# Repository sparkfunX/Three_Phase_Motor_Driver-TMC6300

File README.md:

SparkFun 3-Phase BLDC Motor Driver - TMC6300
========================================

[*SparkFun 3-Phase BLDC Motor Driver - TMC6300(ROB-21220)*](https://www.sparkfun.com/products/21220)

The TMC6300 from Trinamic is a powerful, yet easy to use three phase brushless DC (BLDC) motor driver. Separate high side and low side controls allow for incredible control up to 2A of current. The driver is temperature and short circuit protected with a diagnostic output pin to indicate system issues. With an operating voltage down to 2V, the TMC6300 is suitable for battery powered designs.

We've designed an innovative 2 sided, 4 layer breakout board to make hookup as easy as possible. The board is mounted with LEDs and labels facing up, IC down. This allows the thermal pad on the board to be access if cooling is required. 

Controlling 3-phase BLDC motors is not trivial. This board requires 6 PWM signals to fully control one motor. We've found the [*Arduino Simple Field Oriented Control*](https://docs.simplefoc.com/) library to be very good. The [open loop example](https://github.com/simplefoc/Arduino-FOC/blob/master/examples/motion_control/open_loop_motor_control/open_loop_velocity_example/open_loop_velocity_example.ino) combined with the [6 channel PWM method](https://docs.simplefoc.com/bldcdriver6pwm) and *every* PWM pin on the Arduino Uno gets this board working. Note the [pairs of PWM pins](https://docs.simplefoc.com/bldcdriver6pwm) that must be used. 

This board was designed to control our [3-phase Brushless Gimbal Stabilizer Motor](https://www.sparkfun.com/products/20441) but can be used with any 3-phase motor up to 2A.

SparkFun labored with love to create this code. Feel like supporting open source hardware? 
Buy a [breakout board](https://www.sparkfun.com/products/21220) from SparkFun!

Repository Contents
-------------------

* **/Documents** - Datasheet and User Manual
* **/Hardware** - Eagle design files (.brd, .sch)

License Information
-------------------

This product is _**open source**_! 

Please review the LICENSE.md file for license information. 

If you have any questions or concerns on licensing, please contact techsupport@sparkfun.com.

Please use, reuse, and modify these files as you see fit. Please maintain attribution to SparkFun Electronics and release any derivative under the same license.

Distributed as-is; no warranty is given.

- Your friends at SparkFun.

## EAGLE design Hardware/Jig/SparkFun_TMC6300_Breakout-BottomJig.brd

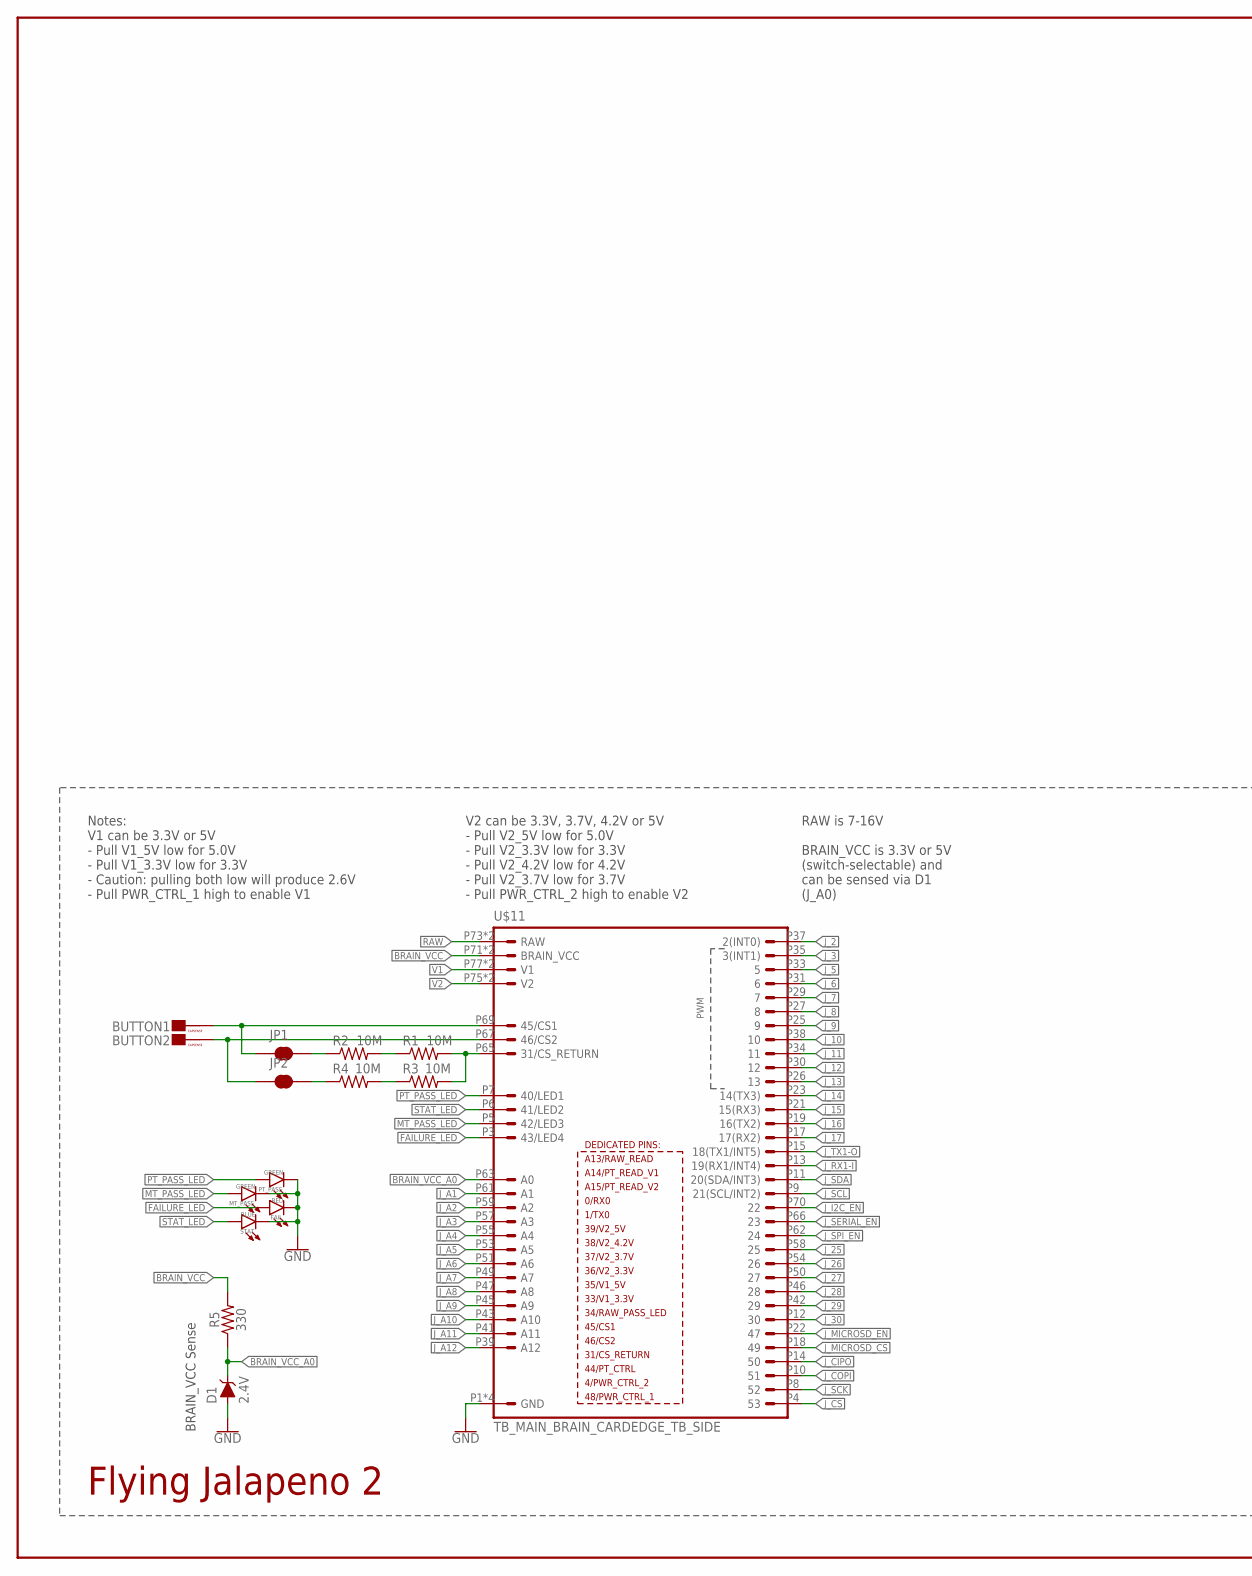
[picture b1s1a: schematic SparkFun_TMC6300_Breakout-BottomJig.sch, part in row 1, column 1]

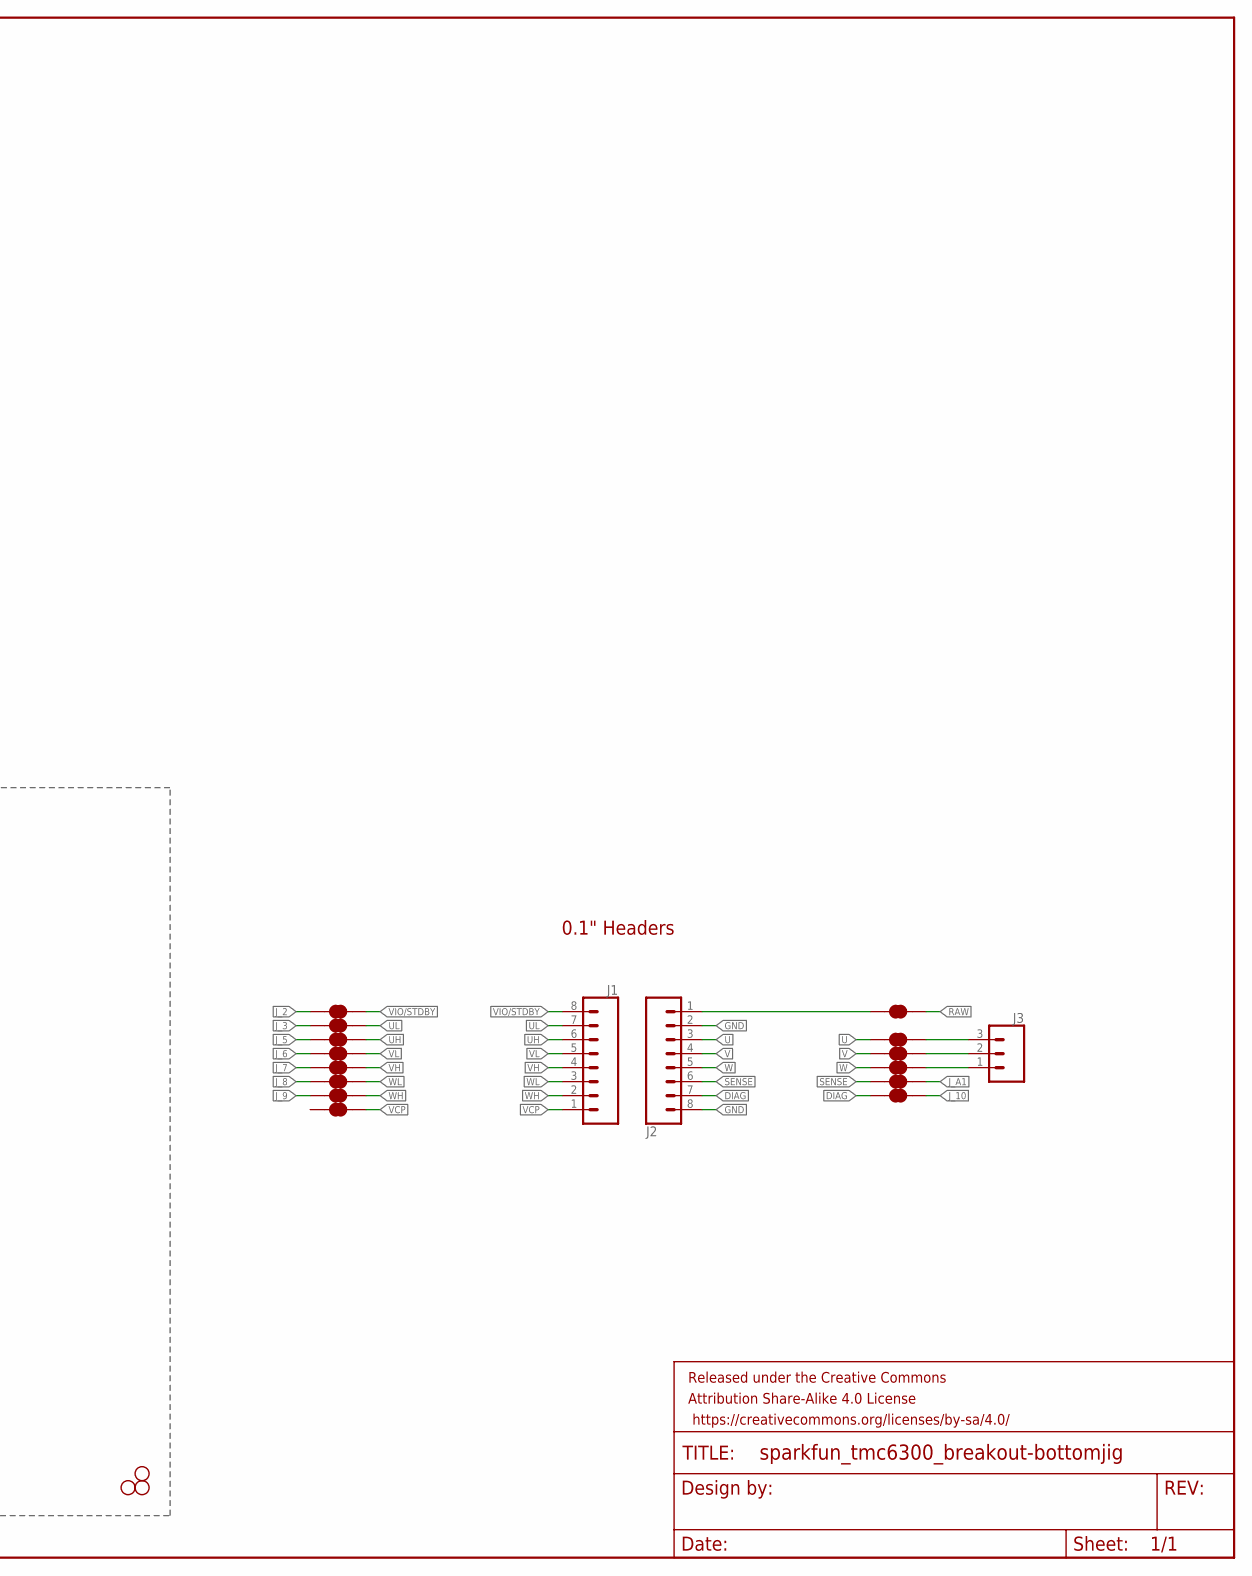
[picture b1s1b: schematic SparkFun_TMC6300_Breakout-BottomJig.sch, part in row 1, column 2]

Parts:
BUTTON1, BUTTON2: CAPSENSE_BUTTON_PAD_ONLYV2_SMALL; CAPSENSE_BUTTON_PAD_ONLY_SM
D1: 2.4V; SOD-323
FAIL: RED; LED-1206
FRAME2: FRAME-LEDGER; CREATIVE_COMMONS
H1, H3, H4: STAND-OFF
J1, J2: CONN_08LOCK_NO_SILK; 1X08_LOCK_NO_SILK
J3: CONN_031X03_NO_SILK; 1X03_NO_SILK
JP1, JP2: JUMPER-SMT_2_NC_TRACE_SILK; SMT-JUMPER_2_NC_TRACE_SILK
J_SCL6, J_SCL7, J_SCL8: JUMPER-SMT_2_NC_TRACE_NO-SILK; SMT-JUMPER_2_NC_TRACE_NO-SILK
J_SDA1, J_SDA2, J_SDA3, J_SDA4, J_SDA5, J_SDA6, J_SDA7, J_SDA8, J_SDA9, J_SDA10, J_SDA11: JUMPER-SMT_2_NC_TRACE_NO-SILK; SMT-JUMPER_2_NC_TRACE_NO-SILK
MT_PASS: GREEN; LED-1206
PT_PASS: GREEN; LED-1206
R1, R2, R3, R4: 10M; 0603
R5: 330; 0603
STAT: BLUE; LED-1206
U$11: TB_MAIN_BRAIN_CARDEDGE_TB_SIDE; TB_CARDEDGE

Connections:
BRAIN_VCC: R5.2, U$11.P71 (BRAIN_VCC), U$11.P72 (BRAIN_VCC)
BRAIN_VCC_A0: D1.C, R5.1, U$11.P63 (A0)
DIAG: J2.7, J_SDA7.1
FAILURE_LED: FAIL.A, U$11.P3 (43/LED4)
GND: D1.A, FAIL.C, J2.2, J2.8, MT_PASS.C, PT_PASS.C, STAT.C, U$11.P1 (GND), U$11.P2 (GND), U$11.P79 (GND), U$11.P80 (GND)
J_2: J_SCL8.1, U$11.P37 (2(INT0))
J_3: J_SCL6.1, U$11.P35 (3(INT1))
J_5: J_SCL7.1, U$11.P33 (5)
J_6: J_SDA2.1, U$11.P31 (6)
J_7: J_SDA3.1, U$11.P29 (7)
J_8: J_SDA4.1, U$11.P27 (8)
J_9: J_SDA5.1, U$11.P25 (9)
J_10: J_SDA7.2, U$11.P38 (10)
J_11: U$11.P34 (11)
J_12: U$11.P30 (12)
J_13: U$11.P26 (13)
J_14: U$11.P23 (14(TX3))
J_15: U$11.P21 (15(RX3))
J_16: U$11.P19 (16(TX2))
J_17: U$11.P17 (17(RX2))
J_25: U$11.P58 (25)
J_26: U$11.P54 (26)
J_27: U$11.P50 (27)
J_28: U$11.P46 (28)
J_29: U$11.P42 (29)
J_30: U$11.P12 (30)
J_A1: J_SDA8.2, U$11.P61 (A1)
J_A2: U$11.P59 (A2)
J_A3: U$11.P57 (A3)
J_A4: U$11.P55 (A4)
J_A5: U$11.P53 (A5)
J_A6: U$11.P51 (A6)
J_A7: U$11.P49 (A7)
J_A8: U$11.P47 (A8)
J_A9: U$11.P45 (A9)
J_A10: U$11.P43 (A10)
J_A11: U$11.P41 (A11)
J_A12: U$11.P39 (A12)
J_CIPO: U$11.P14 (50)
J_COPI: U$11.P10 (51)
J_CS: U$11.P4 (53)
J_I2C_EN: U$11.P70 (22)
J_MICROSD_!CS!: U$11.P18 (49)
J_MICROSD_EN: U$11.P22 (47)
J_RX1-I: U$11.P13 (19(RX1/INT4))
J_SCK: U$11.P8 (52)
J_SCL: U$11.P9 (21(SCL/INT2))
J_SDA: U$11.P11 (20(SDA/INT3))
J_SERIAL_EN: U$11.P66 (23)
J_SPI_EN: U$11.P62 (24)
J_TX1-O: U$11.P15 (18(TX1/INT5))
MT_PASS_LED: MT_PASS.A, U$11.P5 (42/LED3)
unnamed: J3.1, J_SDA9.2
unnamed: R1.2, R3.2, U$11.P65 (31/CS_RETURN)
unnamed: R1.1, R2.2
unnamed: J3.2, J_SDA10.2
unnamed: J3.3, J_SDA11.2
unnamed: J2.1, J_SDA1.1
unnamed: BUTTON1.CAPSENSE_PAD, JP1.1, U$11.P69 (45/CS1)
unnamed: R3.1, R4.2
unnamed: JP2.2, R4.1
unnamed: BUTTON2.CAPSENSE_PAD, JP2.1, U$11.P67 (46/CS2)
unnamed: JP1.2, R2.1
PT_PASS_LED: PT_PASS.A, U$11.P7 (40/LED1)
RAW: J_SDA1.2, U$11.P73 (RAW), U$11.P74 (RAW)
SENSE: J2.6, J_SDA8.1
STAT_LED: STAT.A, U$11.P6 (41/LED2)
U: J2.3, J_SDA11.1
UH: J1.6, J_SCL7.2
UL: J1.7, J_SCL6.2
V: J2.4, J_SDA10.1
V1: U$11.P77 (V1), U$11.P78 (V1)
V2: U$11.P75 (V2), U$11.P76 (V2)
VCP: J1.1, J_SDA6.2
VH: J1.4, J_SDA3.2
VIO/!STDBY!: J1.8, J_SCL8.2
VL: J1.5, J_SDA2.2
W: J2.5, J_SDA9.1
WH: J1.2, J_SDA5.2
WL: J1.3, J_SDA4.2

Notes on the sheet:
0.1" Headers
Flying Jalapeno 2
Notes: V1 can be 3.3V or 5V - Pull V1_5V low for 5.0V - Pull V1_3.3V low for 3.3V - Caution: pulling both low will produce 2.6V - Pull PWR_CTRL_1 high to enable V1
V2 can be 3.3V, 3.7V, 4.2V or 5V - Pull V2_5V low for 5.0V - Pull V2_3.3V low for 3.3V - Pull V2_4.2V low for 4.2V - Pull V2_3.7V low for 3.7V - Pull PWR_CTRL_2 high to enable V2
RAW is 7-16V BRAIN_VCC is 3.3V or 5V (switch-selectable) and can be sensed via D1 (J_A0)
BRAIN_VCC Sense

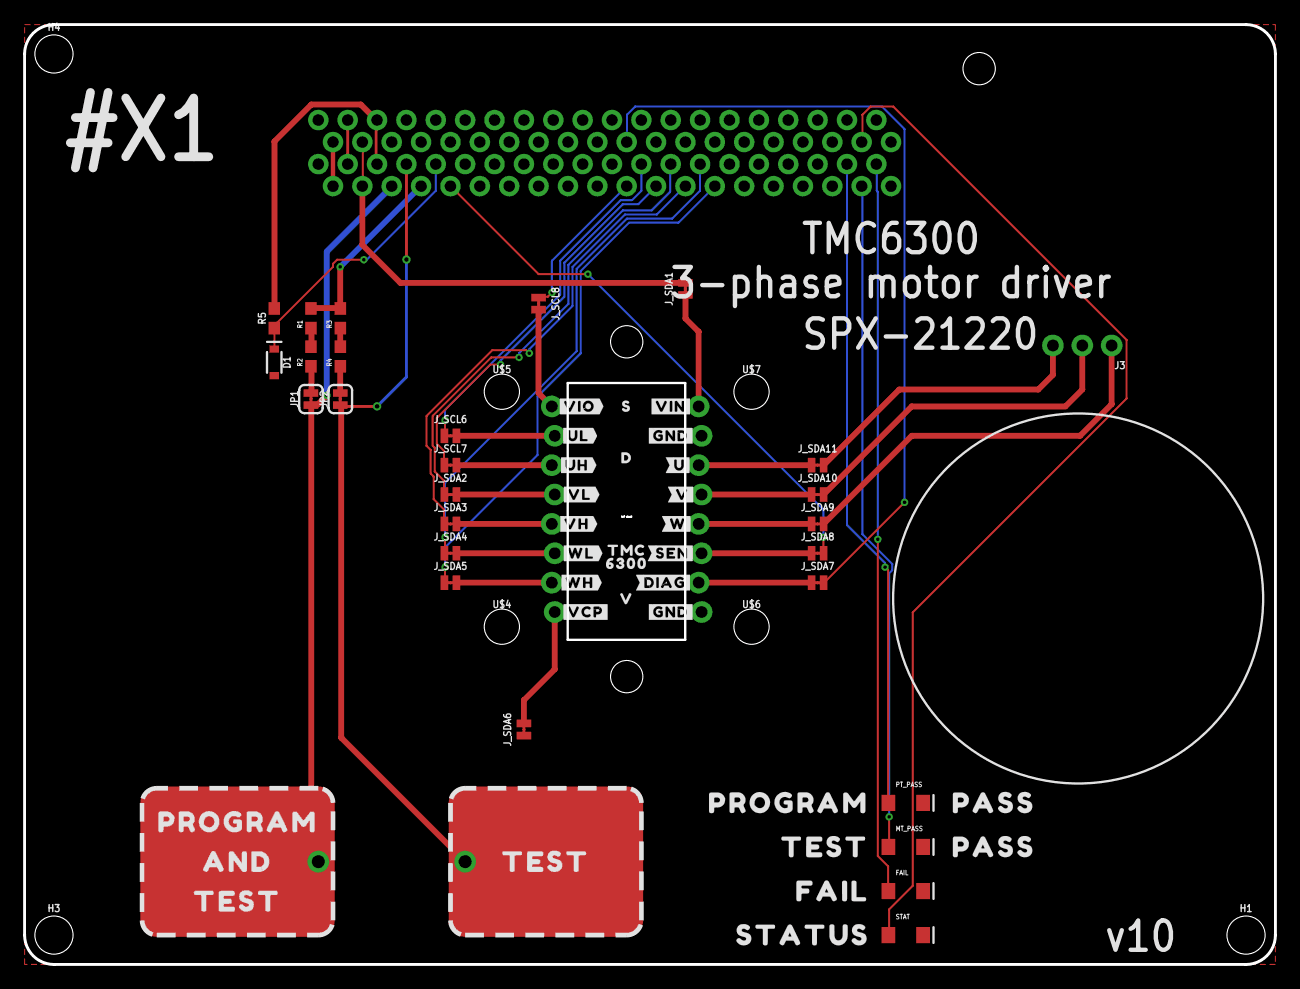
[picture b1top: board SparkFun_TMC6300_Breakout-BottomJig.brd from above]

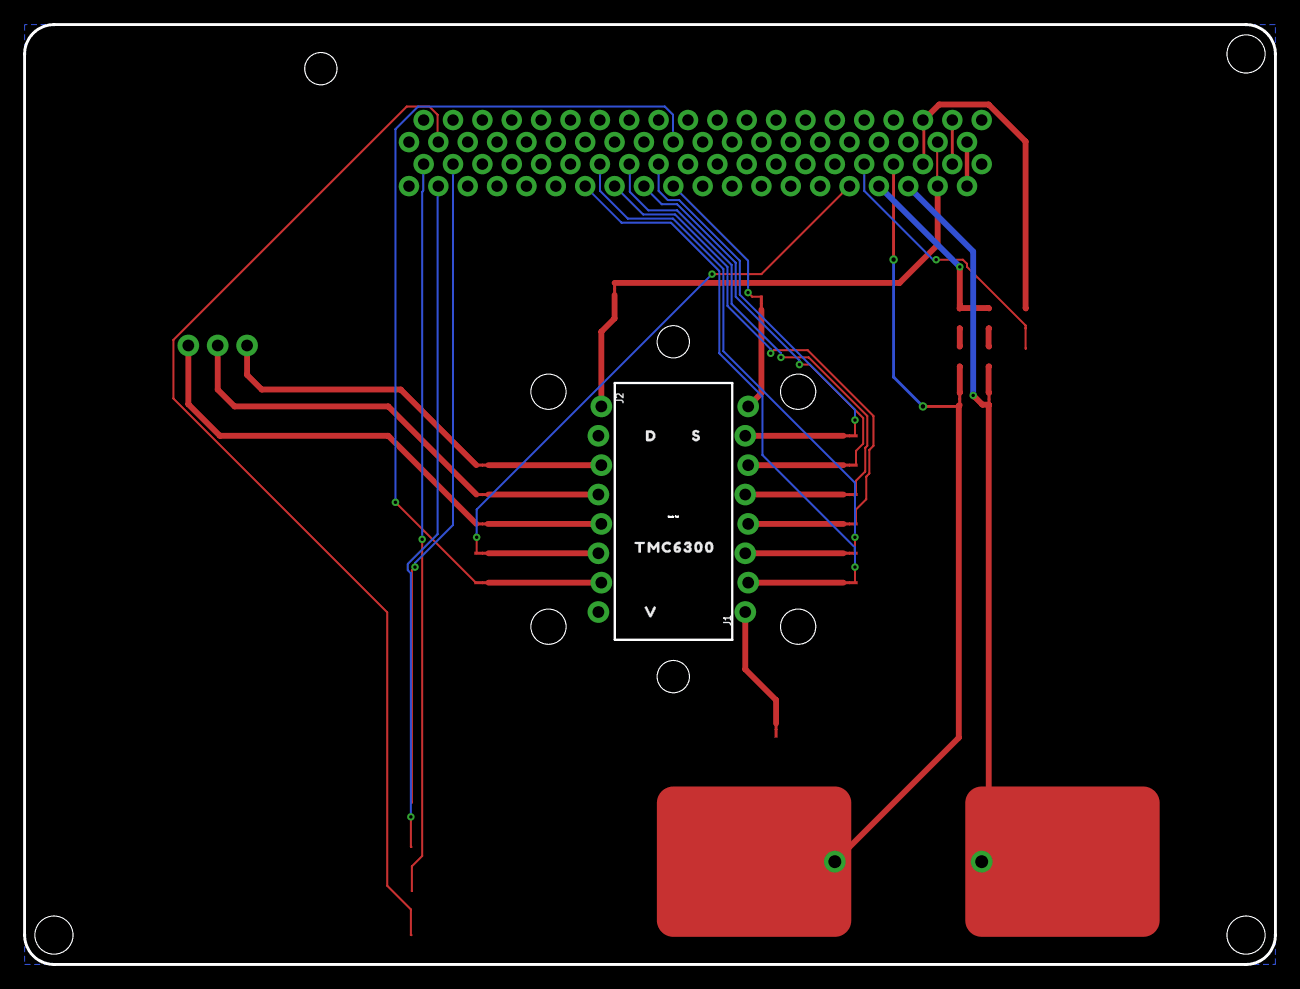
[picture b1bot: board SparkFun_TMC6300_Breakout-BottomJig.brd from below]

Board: 2 copper layers, 108.2 x 81.3 mm, 77 parts (6 on the bottom side), 43 nets.

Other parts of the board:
U$1, U$28: #GND#1
U$2: #SEN#0
U$3: #DIAG#0
U$4, U$5, U$6, U$7: STAND-OFF-TIGHT
U$8, U$10: NUBBIN_LOCKER
U$9: #U#6
U$12: #VCP#0
U$13: #VIO#1
U$14, U$29: PROGRAM0
U$15: 63001
U$16, U$18: D0
U$17: TMC63000
U$19, U$27: S1
U$20, U$26: V2
U$21: #UH#5
U$22: #UL#4
U$23: TMC0
U$24: #VIN#0
U$25: #V#7
U$30: #VH#2
U$31: #VL#3
U$32: #W#8
U$33: #WH#1
U$34: #WL#0
U$35: AND0
U$38, U$39, U$40: TEST0
U$41, U$42: PASS0
U$43: FAIL0
U$44: STATUS0

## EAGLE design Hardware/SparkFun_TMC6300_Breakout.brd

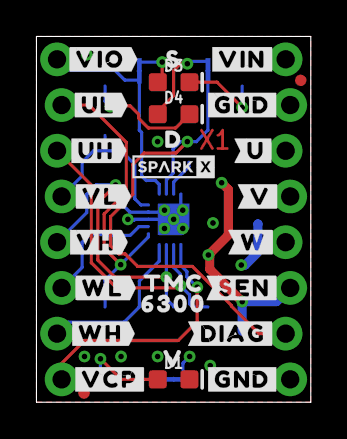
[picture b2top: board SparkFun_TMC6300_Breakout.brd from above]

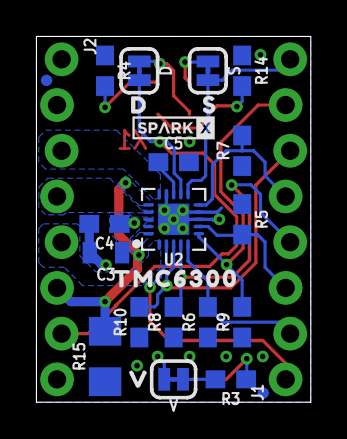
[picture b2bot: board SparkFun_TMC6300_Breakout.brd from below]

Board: 4 copper layers, 15.2 x 20.3 mm, 56 parts (28 on the bottom side), 22 nets.

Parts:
C3: 10uF; 0805
C4, C5: 0.1uF; 0603
D: JUMPER-SMT_2_NC_TRACE_SILK; SMT-JUMPER_2_NC_TRACE_SILK
D1: RED; LED-0603
D3: BLUE; LED-0603
D4: GREEN; LED-0603
FD1, FD2, FD3, FD4: FIDUCIALUFIDUCIAL; FIDUCIAL-MICRO
FRAME1: FRAME-LETTER; CREATIVE_COMMONS
J1, J2: 1X08_LOCK_NO_SILK
LOGO1: OSHW-LOGONO_SILK; DUMMY
LOGO2: SPECIAL_INSTRUCTIONS-ORDERING; ORDERING_INSTRUCTIONS
R3: 1k; 0603
R4, R14: 330; 0603
R5, R6, R7, R8, R9, R10: 100k; 0603
R15: 0.12; 1206
S: JUMPER-SMT_2_NC_TRACE_SILK; SMT-JUMPER_2_NC_TRACE_SILK
U2: TMC6300; QFN-20
U$1, U$28: #GND#1
U$2: #SEN#0
U$3: #DIAG#0
U$9: #U#6
U$12: #VCP#0
U$13: #VIO#1
U$15: 63001
U$16, U$18: D0
U$17: TMC63000
U$19, U$27: S1
U$20, U$26: V2
U$21: #UH#5
U$22: #UL#4
U$23: TMC0
U$24: #VIN#0
U$25: #V#7
U$30: #VH#2
U$31: #VL#3
U$32: #W#8
U$33: #WH#1
U$34: #WL#0
U$36, U$37: SPARKX-LOGO2; SPARKX-TINY
V: JUMPER-SMT_2_NC_TRACE_SILK; SMT-JUMPER_2_NC_TRACE_SILK

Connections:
DIAG: D.2, J2.7, U2.12
GND: C3.2, C4.2, C5.2, D1.C, J2.2, J2.8, R4.1, R5.1, R6.1, R7.1, R8.1, R9.1, R10.1, R14.1, R15.1, U2.8, U2.9, U2.14, U2.PAD
unnamed: R3.2, V.1
unnamed: D1.A, R3.1
unnamed: D3.A, S.1
unnamed: C5.1, U2.13
unnamed: D.1, D4.A
unnamed: D3.C, R4.2
unnamed: D4.C, R14.2
SENSE: J2.6, R15.2, U2.16, U2.20
U: J2.3, U2.15
UH: J1.6, R10.2, U2.3
UL: J1.7, R9.2, U2.6
V: J2.4, U2.17
VCP: J1.1, U2.2
VH: J1.4, R8.2, U2.4
VIN: C3.1, C4.1, J2.1, U2.18, V.2
VIO/!STDBY!: J1.8, S.2, U2.11
VL: J1.5, R7.2, U2.10
W: J2.5, U2.1
WH: J1.2, R6.2, U2.5
WL: J1.3, R5.2, U2.7

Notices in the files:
parts and their libraries:
SparkFun-Aesthetics: Licensing: Creative Commons ShareAlike 4.0 International - https://creativecommons.org/licenses/by-sa/4.0
SparkFun-Aesthetics: Released under the Creative Commons Attribution Share-Alike 4.0 License
SparkFun-Aesthetics: https://creativecommons.org/licenses/by-sa/4.0
